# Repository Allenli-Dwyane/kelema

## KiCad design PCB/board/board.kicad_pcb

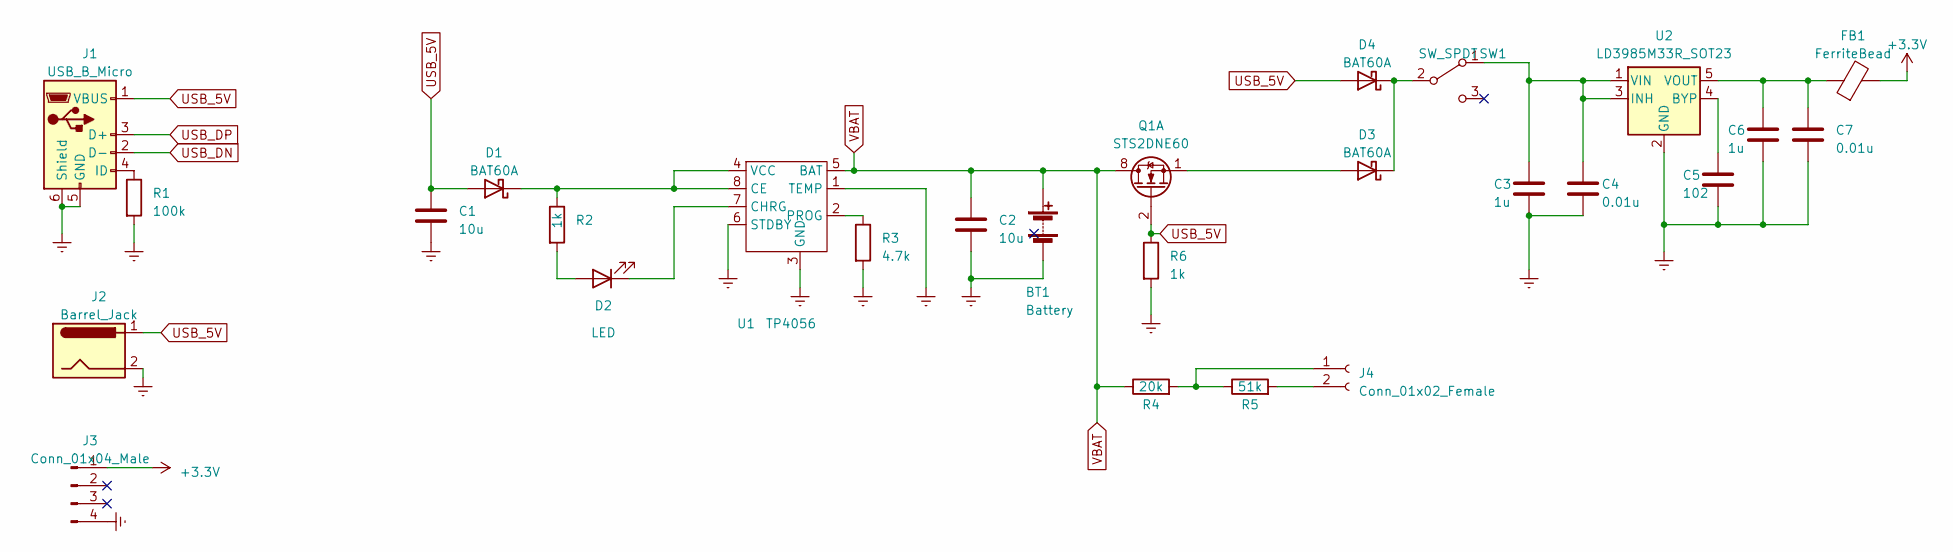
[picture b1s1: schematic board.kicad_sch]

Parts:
BT1: Battery; PinSocket_1x02_P2.54mm_Vertical
C1, C2: 10u; C_0805_2012Metric_Pad1.18x1.45mm_HandSolder
C3, C6: 1u; C_0805_2012Metric_Pad1.18x1.45mm_HandSolder
C4, C7: 0.01u; C_0805_2012Metric_Pad1.18x1.45mm_HandSolder
C5: 102; C_0805_2012Metric_Pad1.18x1.45mm_HandSolder
D1, D3, D4: BAT60A; D_SOD-323
D2: LED; LED_0805_2012Metric_Pad1.15x1.40mm_HandSolder
FB1: FerriteBead; R_0805_2012Metric_Pad1.20x1.40mm_HandSolder
J1: USB_B_Micro; USB_Micro-B_Wuerth_629105150521_CircularHoles
J2: Barrel_Jack; BarrelJack_Horizontal
J3: Conn_01x04_Male; PinSocket_1x04_P2.54mm_Vertical
J4: Conn_01x02_Female; PinSocket_1x02_P2.54mm_Vertical
Q1: STS2DNE60; SOIC-8_3.9x4.9mm_P1.27mm
R1: 100k; R_0805_2012Metric_Pad1.20x1.40mm_HandSolder
R2, R6: 1k; R_0805_2012Metric_Pad1.20x1.40mm_HandSolder
R3: 4.7k; R_0805_2012Metric_Pad1.20x1.40mm_HandSolder
R4: 20k; R_0805_2012Metric_Pad1.20x1.40mm_HandSolder
R5: 51k; R_0805_2012Metric_Pad1.20x1.40mm_HandSolder
SW1: SW_SPDT; SW_CuK_OS102011MA1QN1_SPDT_Angled
U1: TP4056; SOP-8_3.9x4.9mm_P1.27mm
U2: LD3985M33R_SOT23; SOT-23-5

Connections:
+3V3: FB1.2, J3.1
Earth: BT1.2 (-), C1.2, C2.2, C3.2, C4.2, C5.2, C6.2, C7.2, J1.5 (GND), J1.6 (Shield), J2.2, J3.4, R1.2, R3.2, R6.2, U1.1 (TEMP), U1.3 (GND), U1.6 (STDBY), U2.2 (GND)
unnamed: C3.1, C4.1, SW1.1 (A), U2.1 (VIN), U2.3 (INH)
unnamed: C5.1, U2.4 (BYP)
unnamed: C6.1, C7.1, FB1.1, U2.5 (VOUT)
unnamed: D1.1 (K), R2.1, U1.4 (VCC), U1.8 (CE)
unnamed: D2.1 (K), U1.7 (CHRG)
unnamed: D2.2 (A), R2.2
unnamed: D3.1 (K), D4.1 (K), SW1.2 (B)
unnamed: D3.2 (A), Q1.1 (S1)
unnamed: J1.4 (ID), R1.1
unnamed: J4.1, R4.2, R5.1
unnamed: J4.2, R5.2
unnamed: R3.1, U1.2 (PROG)
USB_5V: C1.1, D1.2 (A), D4.2 (A), J1.1 (VBUS), J2.1, Q1.2 (G1), R6.1
USB_DN: J1.2 (D-)
USB_DP: J1.3 (D+)
VBAT: BT1.1 (+), C2.1, Q1.7 (D1), Q1.8 (D1), R4.1, U1.5 (BAT)

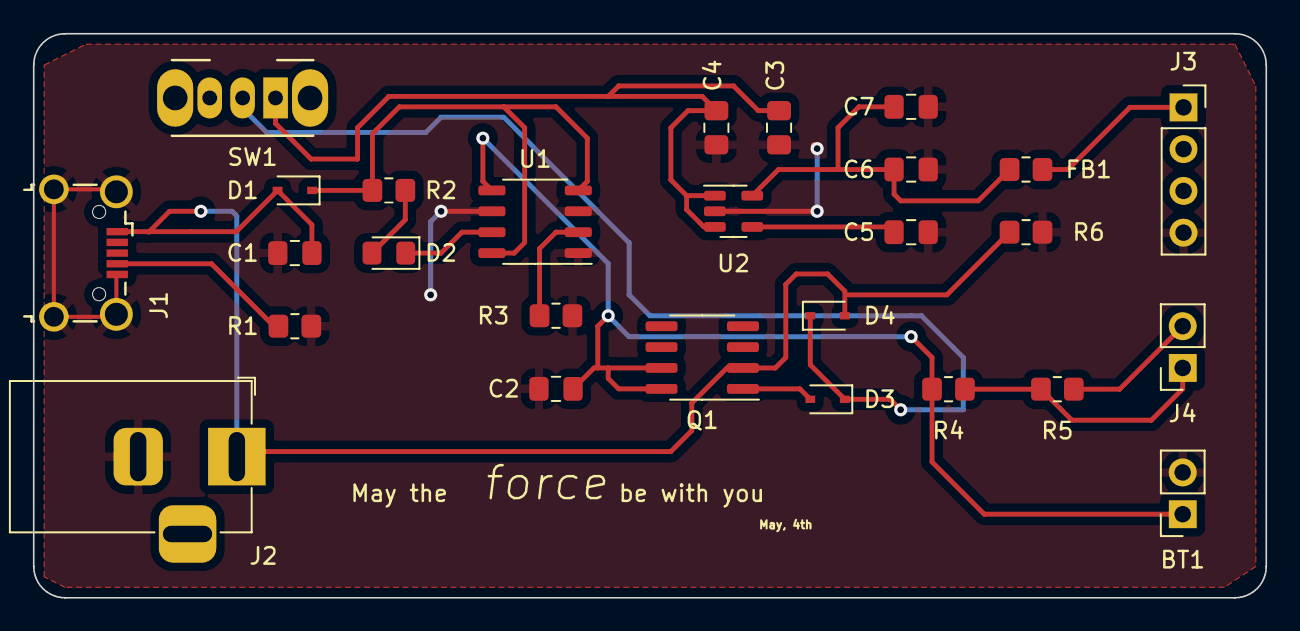
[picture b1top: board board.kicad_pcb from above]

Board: 2 copper layers, 74.9 x 34.3 mm, 27 parts (0 on the bottom side), 16 nets.

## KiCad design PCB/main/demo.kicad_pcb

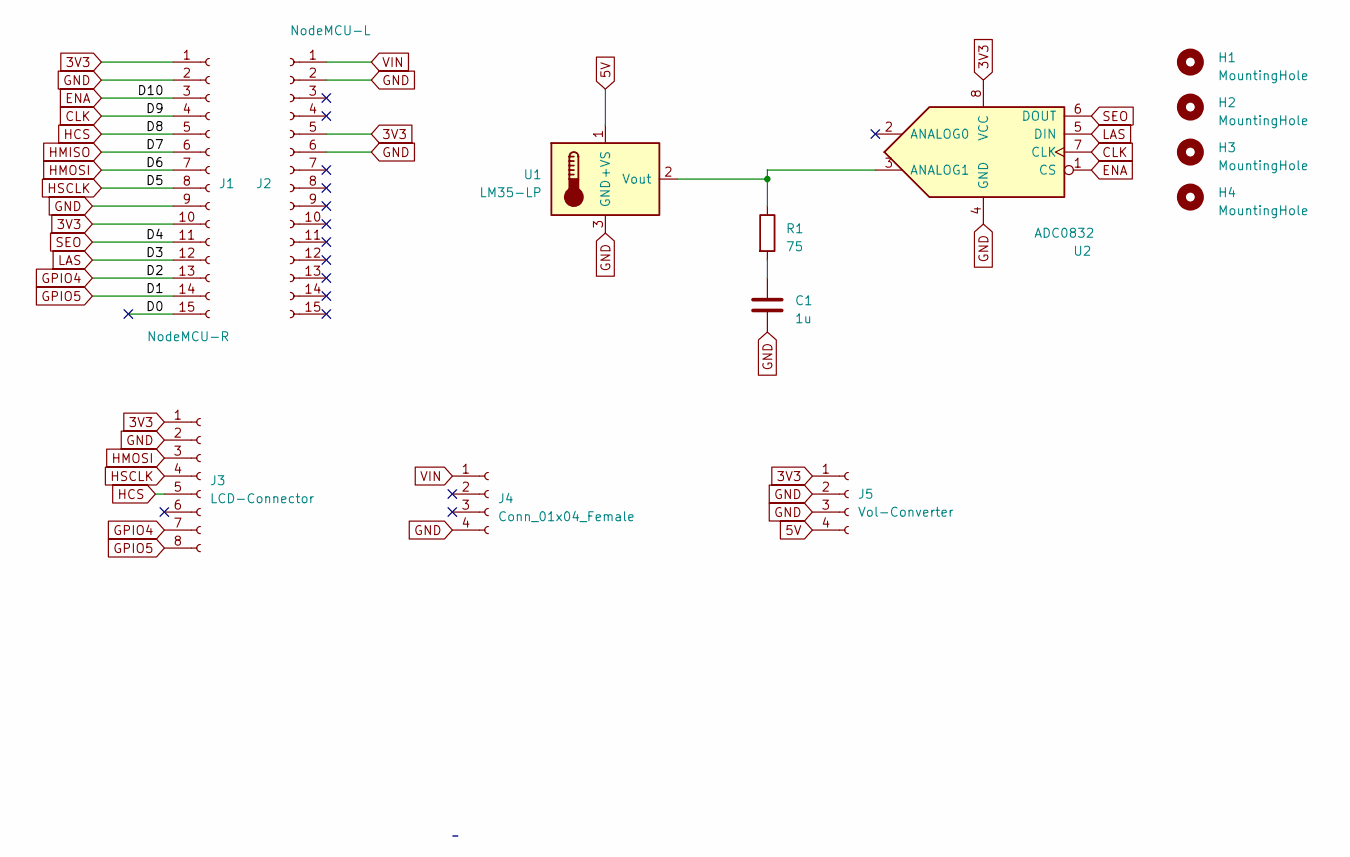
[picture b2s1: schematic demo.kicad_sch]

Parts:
C1: 1u; C_0805_2012Metric_Pad1.18x1.45mm_HandSolder
H1, H2, H3, H4: MountingHole; MountingHole_2.2mm_M2_ISO7380
J1: NodeMCU-R; PinHeader_1x15_P2.54mm_Vertical
J2: NodeMCU-L; PinHeader_1x15_P2.54mm_Vertical
J3: LCD-Connector; PinHeader_1x08_P2.54mm_Vertical
J4: Conn_01x04_Female; PinHeader_1x04_P2.54mm_Vertical
J5: Vol-Converter
R1: 75; R_0805_2012Metric_Pad1.20x1.40mm_HandSolder
U1: LM35-LP; TO-92
U2: ADC0832; DIP-8_W7.62mm_LongPads

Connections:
3V3: J1.1, J1.10, J2.5, J3.1, J5.1, U2.8 (VCC)
5V: J5.4, U1.1 (+VS)
/D0: J1.15
CLK: J1.4, U2.7 (CLK)
ENA: J1.3, U2.1 (CS)
GND: C1.2, J1.2, J1.9, J2.2, J2.6, J3.2, J4.4, J5.2, J5.3, U1.3 (GND), U2.4 (GND)
GPIO4: J1.13, J3.7
GPIO5: J1.14, J3.8
HCS: J1.5, J3.5
HMISO: J1.6
HMOSI: J1.7, J3.3
HSCLK: J1.8, J3.4
LAS: J1.12, U2.5 (DIN)
unnamed: C1.1, R1.2
unnamed: R1.1, U1.2 (Vout), U2.3 (ANALOG1)
SEO: J1.11, U2.6 (DOUT)
VIN: J2.1, J4.1

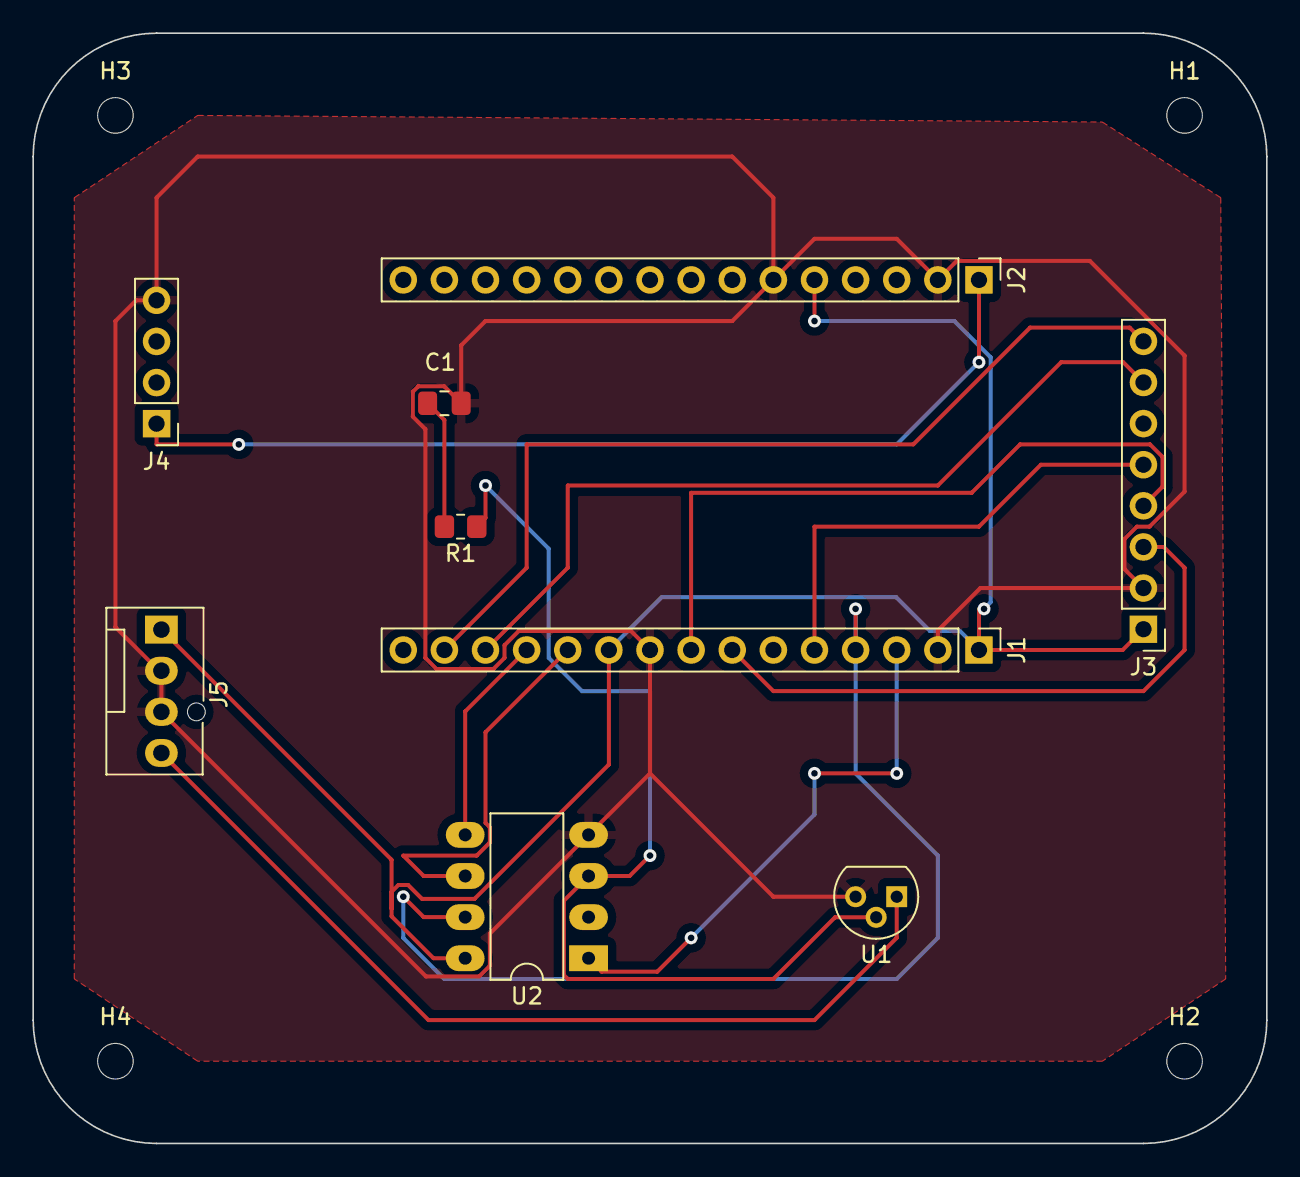
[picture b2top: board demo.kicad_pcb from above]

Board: 2 copper layers, 76.2 x 68.6 mm, 13 parts (0 on the bottom side), 15 nets.

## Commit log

2022-04-18 Add TFT module
2022-05-09 wifi
2022-05-30 add PCB files
2022-06-03 Add Android app codes(in kotlin)
